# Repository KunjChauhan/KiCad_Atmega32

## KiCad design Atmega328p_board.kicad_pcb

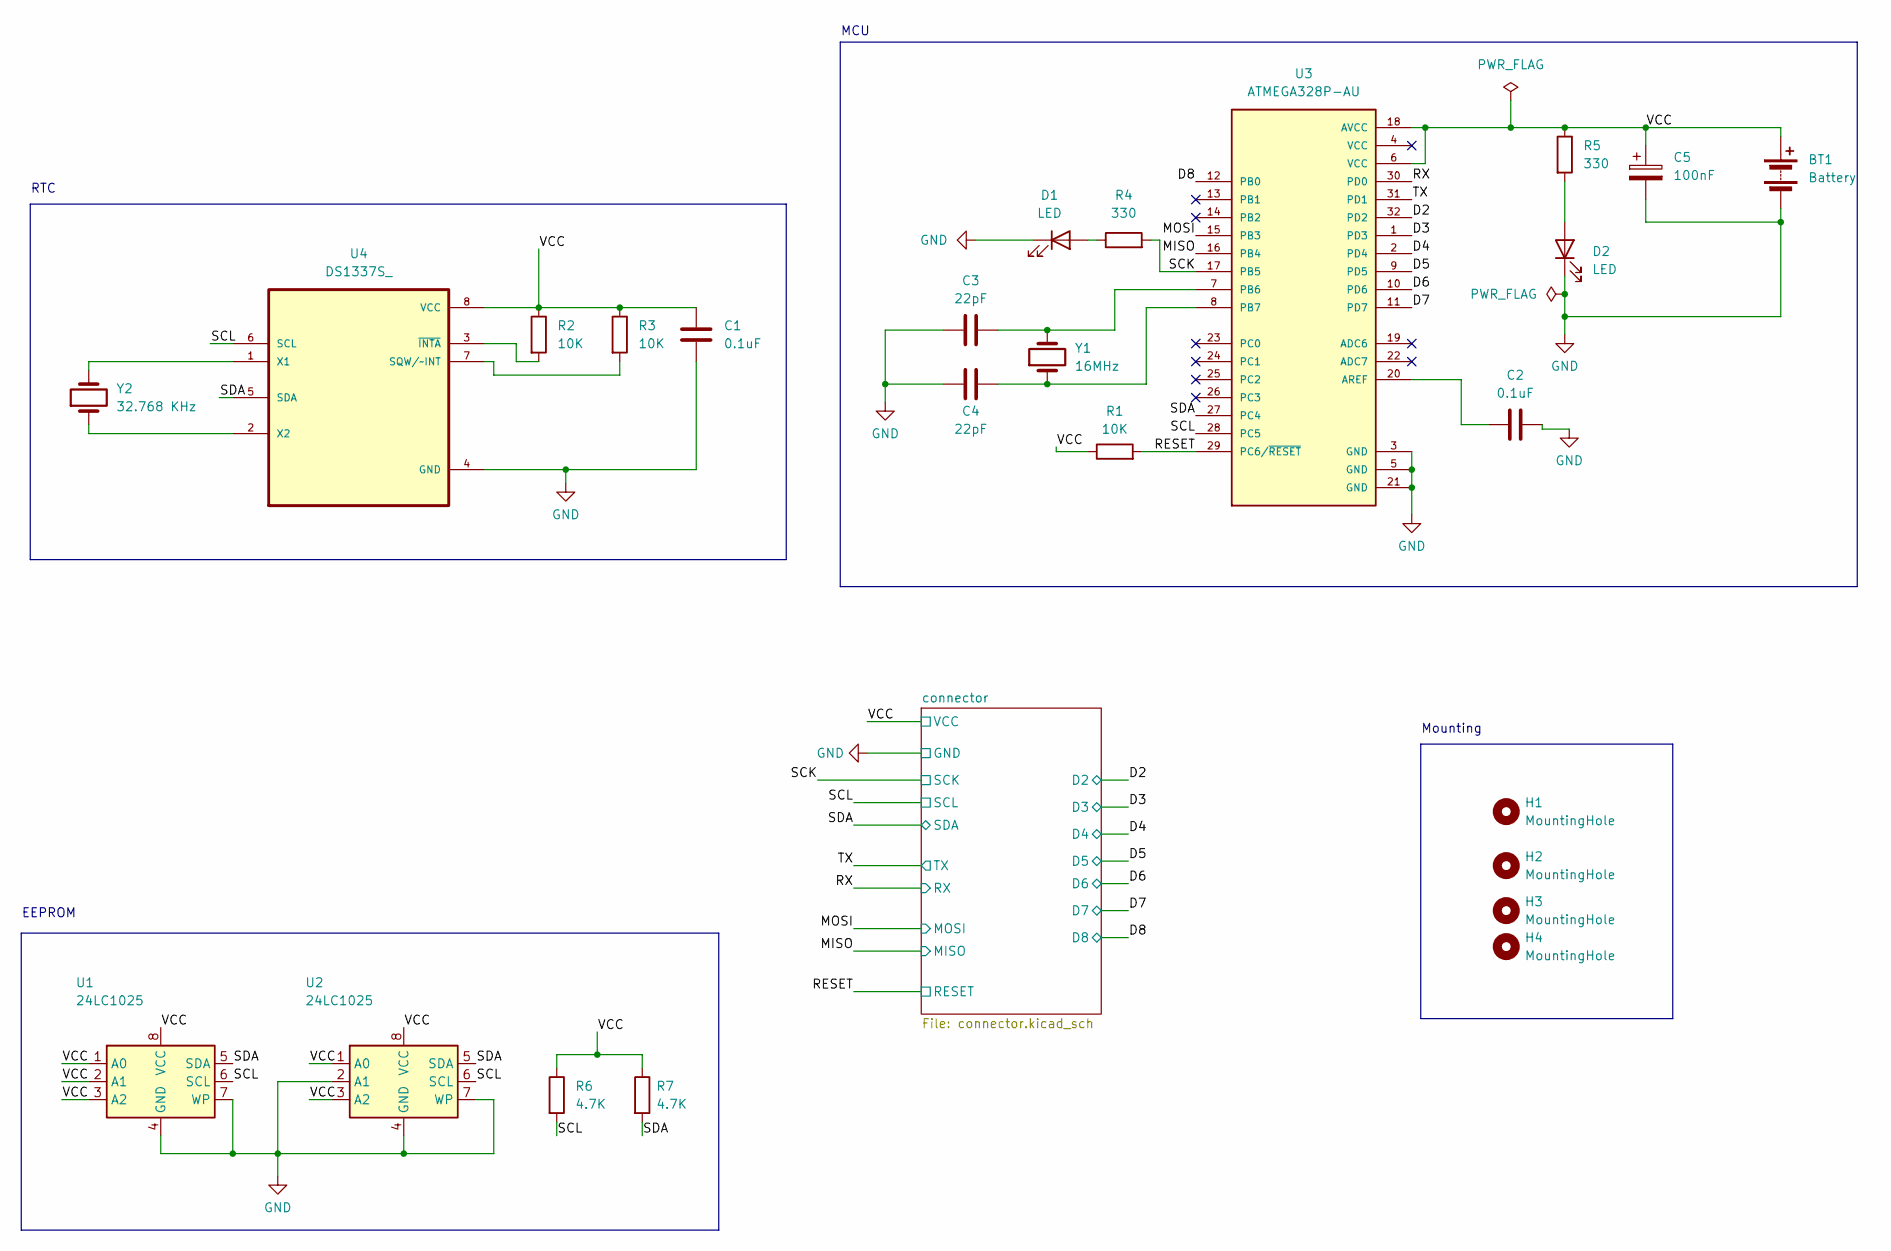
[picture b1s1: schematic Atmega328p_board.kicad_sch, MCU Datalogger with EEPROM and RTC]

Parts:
BT1: Battery; PinHeader_1x02_P2.54mm_Vertical
C1, C2: 0.1uF; C_0805_2012Metric
C3, C4: 22pF; C_0805_2012Metric
C5: 100nF; C_0805_2012Metric
D1, D2: LED; LED_0805_2012Metric
H1, H2, H3, H4: MountingHole; MountingHole_2.1mm
R1, R2, R3: 10K; R_0805_2012Metric
R4, R5: 330; R_0805_2012Metric
R6, R7: 4.7K; R_0805_2012Metric
U1, U2: 24LC1025; SOIC-8_5.275x5.275mm_P1.27mm
U3: ATMEGA328P-AU; QFP80P900X900X120-32N; PARTREV 8271A
U4: DS1337S_; SOIC127P600X175-8N
Y1: 16MHz; Crystal_SMD_5032-2Pin_5.0x3.2mm_HandSoldering
Y2: 32.768 KHz; Crystal_SMD_5032-2Pin_5.0x3.2mm_HandSoldering

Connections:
/D2: U3.32 (PD2); also elsewhere on the board
/D3: U3.1 (PD3); also elsewhere on the board
/D4: U3.2 (PD4); also elsewhere on the board
/D5: U3.9 (PD5); also elsewhere on the board
/D6: U3.10 (PD6); also elsewhere on the board
/D7: U3.11 (PD7); also elsewhere on the board
/D8: U3.12 (PB0); also elsewhere on the board
/MISO: U3.16 (PB4); also elsewhere on the board
/MOSI: U3.15 (PB3); also elsewhere on the board
/RESET: R1.2, U3.29 (PC6/~RESET); also elsewhere on the board
/RX: U3.30 (PD0); also elsewhere on the board
/SCK: R4.2, U3.17 (PB5); also elsewhere on the board
/SCL: R6.2, U1.6 (SCL), U2.6 (SCL), U3.28 (PC5), U4.6 (SCL); also elsewhere on the board
/SDA: R7.2, U1.5 (SDA), U2.5 (SDA), U3.27 (PC4), U4.5 (SDA); also elsewhere on the board
/TX: U3.31 (PD1); also elsewhere on the board
/VCC: BT1.1 (+), C1.1, C5.1, R1.1, R2.1, R3.1, R5.1, R6.1, R7.1, U1.1 (A0), U1.2 (A1), U1.3 (A2), U1.8 (VCC), U2.1 (A0), U2.3 (A2), U2.8 (VCC), U3.6 (VCC), U3.18 (AVCC), U4.8 (VCC); also elsewhere on the board
GND: BT1.2 (-), C1.2, C2.2, C3.1, C4.2, C5.2, D1.1 (K), D2.1 (K), U1.4 (GND), U1.7 (WP), U2.2 (A1), U2.4 (GND), U2.7 (WP), U3.3 (GND), U3.5 (GND), U3.21 (GND), U4.4 (GND); also elsewhere on the board
unnamed: D1.2 (A), R4.1
unnamed: D2.2 (A), R5.2
unnamed: C2.1, U3.20 (AREF)
unnamed: C3.2, U3.7 (PB6), Y1.2
unnamed: C4.1, U3.8 (PB7), Y1.1
unnamed: R3.2, U4.7 (SQW/~INT)
unnamed: U4.1 (X1), Y2.2
unnamed: U4.2 (X2), Y2.1
unnamed: R2.2, U4.3 (~INTA)

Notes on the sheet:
EEPROM
MCU
Mounting
RTC

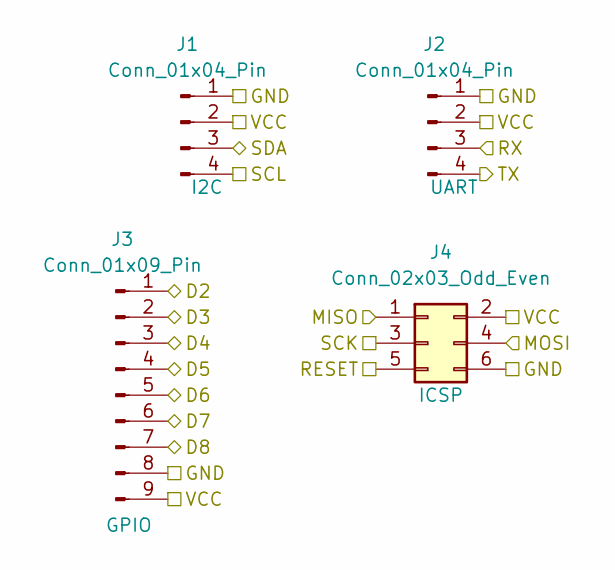
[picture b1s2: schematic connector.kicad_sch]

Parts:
J1, J2: Conn_01x04_Pin; PinHeader_1x04_P2.54mm_Vertical
J3: Conn_01x09_Pin; PinHeader_1x09_P2.54mm_Vertical
J4: Conn_02x03_Odd_Even; PinHeader_2x03_P2.54mm_Vertical

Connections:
/D2: J3.1; also elsewhere on the board
/D3: J3.2; also elsewhere on the board
/D4: J3.3; also elsewhere on the board
/D5: J3.4; also elsewhere on the board
/D6: J3.5; also elsewhere on the board
/D7: J3.6; also elsewhere on the board
/D8: J3.7; also elsewhere on the board
/MISO: J4.1; also elsewhere on the board
/MOSI: J4.4; also elsewhere on the board
/RESET: J4.5; also elsewhere on the board
/RX: J2.3; also elsewhere on the board
/SCK: J4.3; also elsewhere on the board
/SCL: J1.4; also elsewhere on the board
/SDA: J1.3; also elsewhere on the board
/TX: J2.4; also elsewhere on the board
/VCC: J1.2, J2.2, J3.9, J4.2; also elsewhere on the board
GND: J1.1, J2.1, J3.8, J4.6; also elsewhere on the board

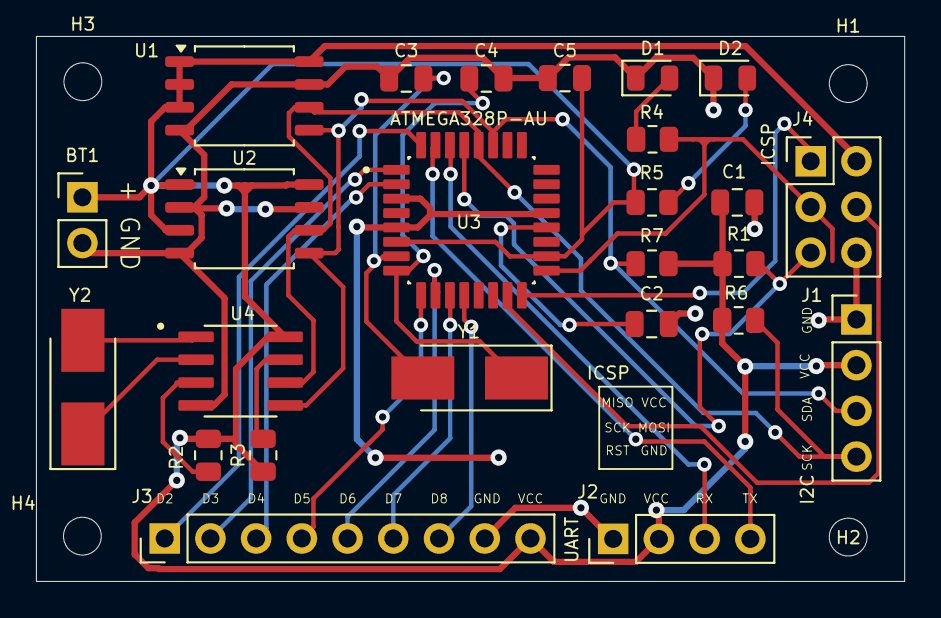
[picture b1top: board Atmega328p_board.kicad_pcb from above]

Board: 2 copper layers, 48.2 x 30.3 mm, 29 parts (0 on the bottom side), 26 nets.

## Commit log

2024-06-16 first commit.
2024-06-16 added symbols in the schematic sheet
2024-06-16 changed symbol position(arranged)
2024-06-16 added values of all the components
2024-06-16 added footprints to all the symbol
2024-06-16 Completed wiring of sheet 1
2024-06-16 Completed wiring of sheet 2
2024-06-16 Allocated power and gnd to POWER netclass
2024-06-16 Completed commits
2024-06-17 Setup PCBnew
2024-06-17 COMPLETED PLACEMENTS OF FOOTPRINTS.
2024-06-17 Routing completed.
2024-06-17 Changed GND copper layer to hatched pattern.
2024-06-17 Refined some routes
2024-06-17 COmpleted with silkscreen and footprints(logo).
2024-06-18 2layer PCB completed
2024-06-18 edited gitignore file
2024-06-18 Completed 4 layer pcb routing
2024-06-18 gitignore updated
2024-06-18 gitiattributes added to ignore pcb files during merge
2024-06-18 2 detects are resolved in schematic
2024-06-18 2 layer pcb fixed with changes of sck and scl
2024-06-18 4 layer pcb fixed with changes of sck and scl
